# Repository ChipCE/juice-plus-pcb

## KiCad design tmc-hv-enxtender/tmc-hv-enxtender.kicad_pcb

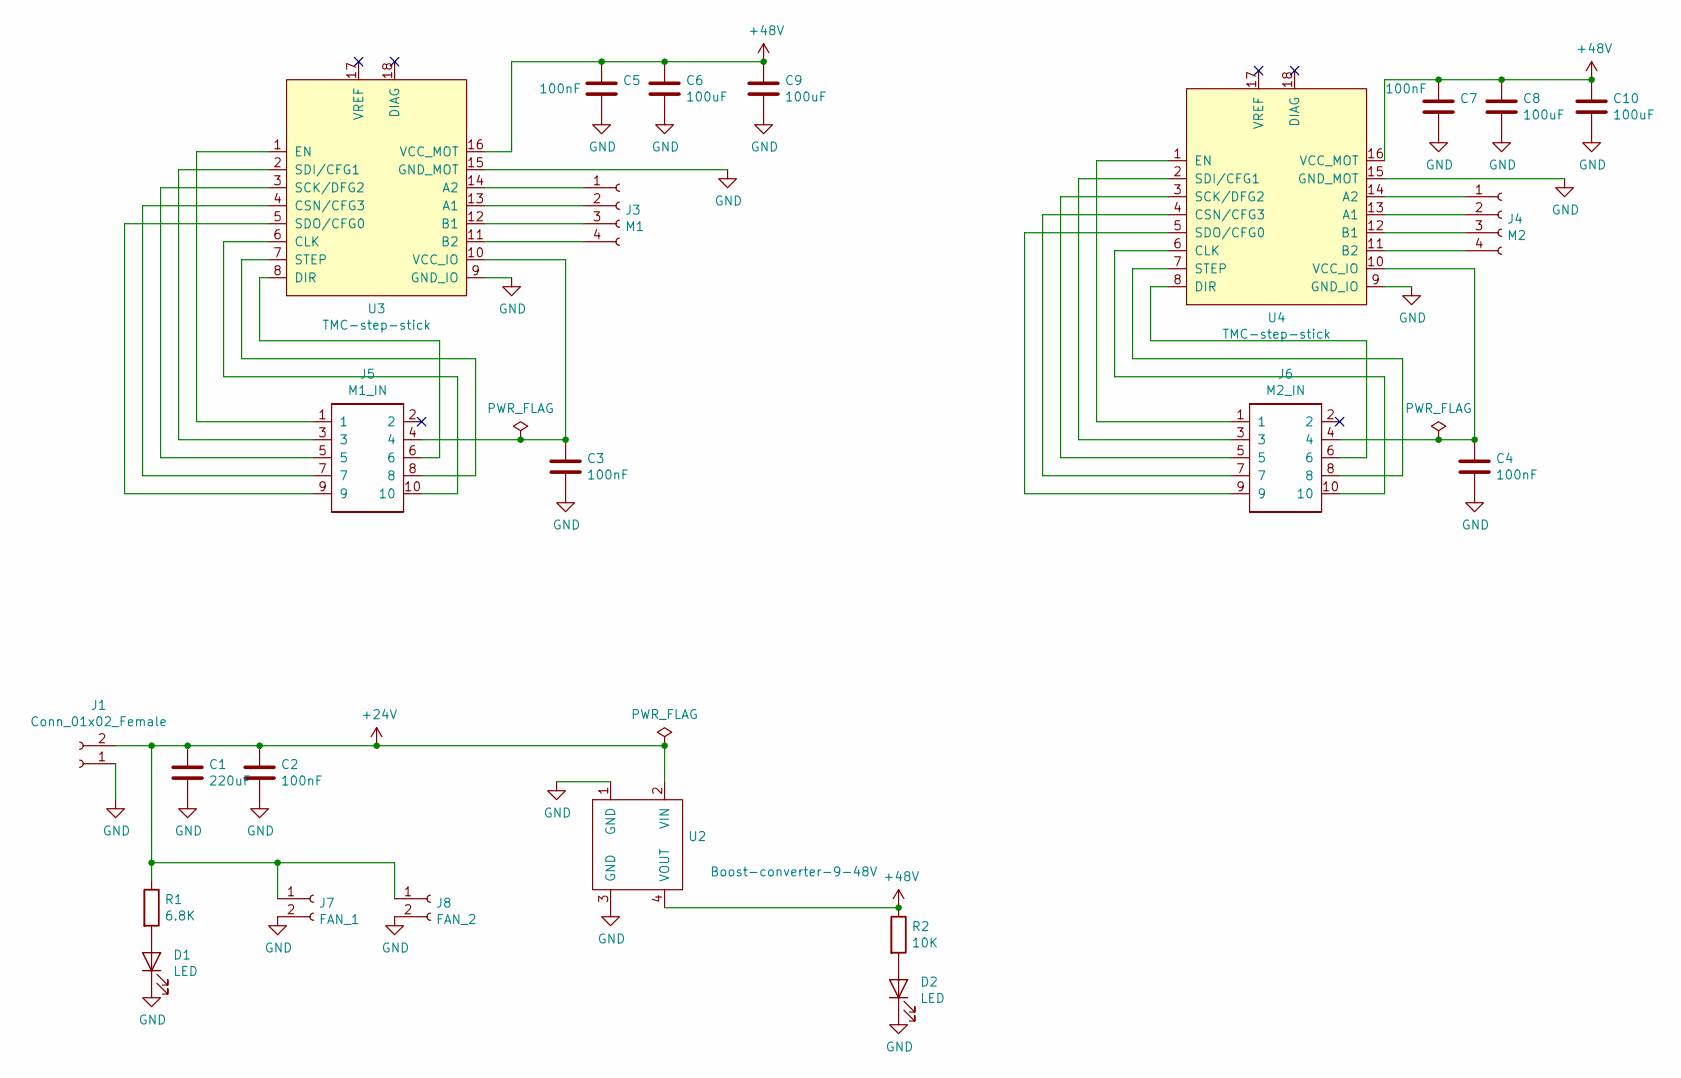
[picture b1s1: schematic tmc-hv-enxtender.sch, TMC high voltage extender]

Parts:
C1: 220uF; CP_Radial_D8.0mm_P3.50mm
C2, C5, C7: 100nF; C_1210_3225Metric
C3, C4: 100nF; C_0805_2012Metric_Pad1.15x1.40mm_HandSolder
C6, C8, C9, C10: 100uF; CP_Radial_D10.0mm_P5.00mm
D1, D2: LED; LED_0805_2012Metric_Castellated
J1: Conn_01x02_Female; TerminalBlock_Phoenix_PT-1,5-2-5.0-H_1x02_P5.00mm_Horizontal
J3: M1; JST_XH_B04B-XH-A_1x04_P2.50mm_Vertical
J4: M2; JST_XH_B04B-XH-A_1x04_P2.50mm_Vertical
J5: M1_IN; IDC-Header_2x05_P2.54mm_Vertical
J6: M2_IN; IDC-Header_2x05_P2.54mm_Vertical
J7: FAN_1; JST_XH_B02B-XH-A_1x02_P2.50mm_Vertical
J8: FAN_2; JST_XH_B02B-XH-A_1x02_P2.50mm_Vertical
R1: 6.8K; R_0805_2012Metric_Pad1.15x1.40mm_HandSolder
R2: 10K; R_0805_2012Metric_Pad1.15x1.40mm_HandSolder
U2: Boost-converter-9-48V; boost-converter-9-48V
U3, U4: TMC-step-stick

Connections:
+24V: C1.1, C2.1, J1.2, J7.1, J8.1, R1.1, U2.2 (VIN)
+48V: C5.1, C6.1, C7.1, C8.1, C9.1, C10.1, R2.1, U2.4 (VOUT), U3.16 (VCC_MOT), U4.16 (VCC_MOT)
GND: C1.2, C2.2, C3.2, C4.2, C5.2, C6.2, C7.2, C8.2, C9.2, C10.2, D1.1 (K), D2.1 (K), J1.1, J7.2, J8.2, U2.1 (GND), U2.3 (GND), U3.9 (GND_IO), U3.15 (GND_MOT), U4.9 (GND_IO), U4.15 (GND_MOT)
unnamed: C3.1, J5.4, U3.10 (VCC_IO)
unnamed: C4.1, J6.4, U4.10 (VCC_IO)
unnamed: D1.2 (A), R1.2
unnamed: D2.2 (A), R2.2
unnamed: J3.1, U3.14 (A2)
unnamed: J3.2, U3.13 (A1)
unnamed: J3.3, U3.12 (B1)
unnamed: J3.4, U3.11 (B2)
unnamed: J4.1, U4.14 (A2)
unnamed: J4.2, U4.13 (A1)
unnamed: J4.3, U4.12 (B1)
unnamed: J4.4, U4.11 (B2)
unnamed: J5.1, U3.1 (EN)
unnamed: J5.3, U3.2 (SDI/CFG1)
unnamed: J5.5, U3.3 (SCK/DFG2)
unnamed: J5.6, U3.8 (DIR)
unnamed: J5.7, U3.4 (CSN/CFG3)
unnamed: J5.8, U3.7 (STEP)
unnamed: J5.9, U3.5 (SDO/CFG0)
unnamed: J5.10, U3.6 (CLK)
unnamed: J6.1, U4.1 (EN)
unnamed: J6.3, U4.2 (SDI/CFG1)
unnamed: J6.5, U4.3 (SCK/DFG2)
unnamed: J6.6, U4.8 (DIR)
unnamed: J6.7, U4.4 (CSN/CFG3)
unnamed: J6.8, U4.7 (STEP)
unnamed: J6.9, U4.5 (SDO/CFG0)
unnamed: J6.10, U4.6 (CLK)

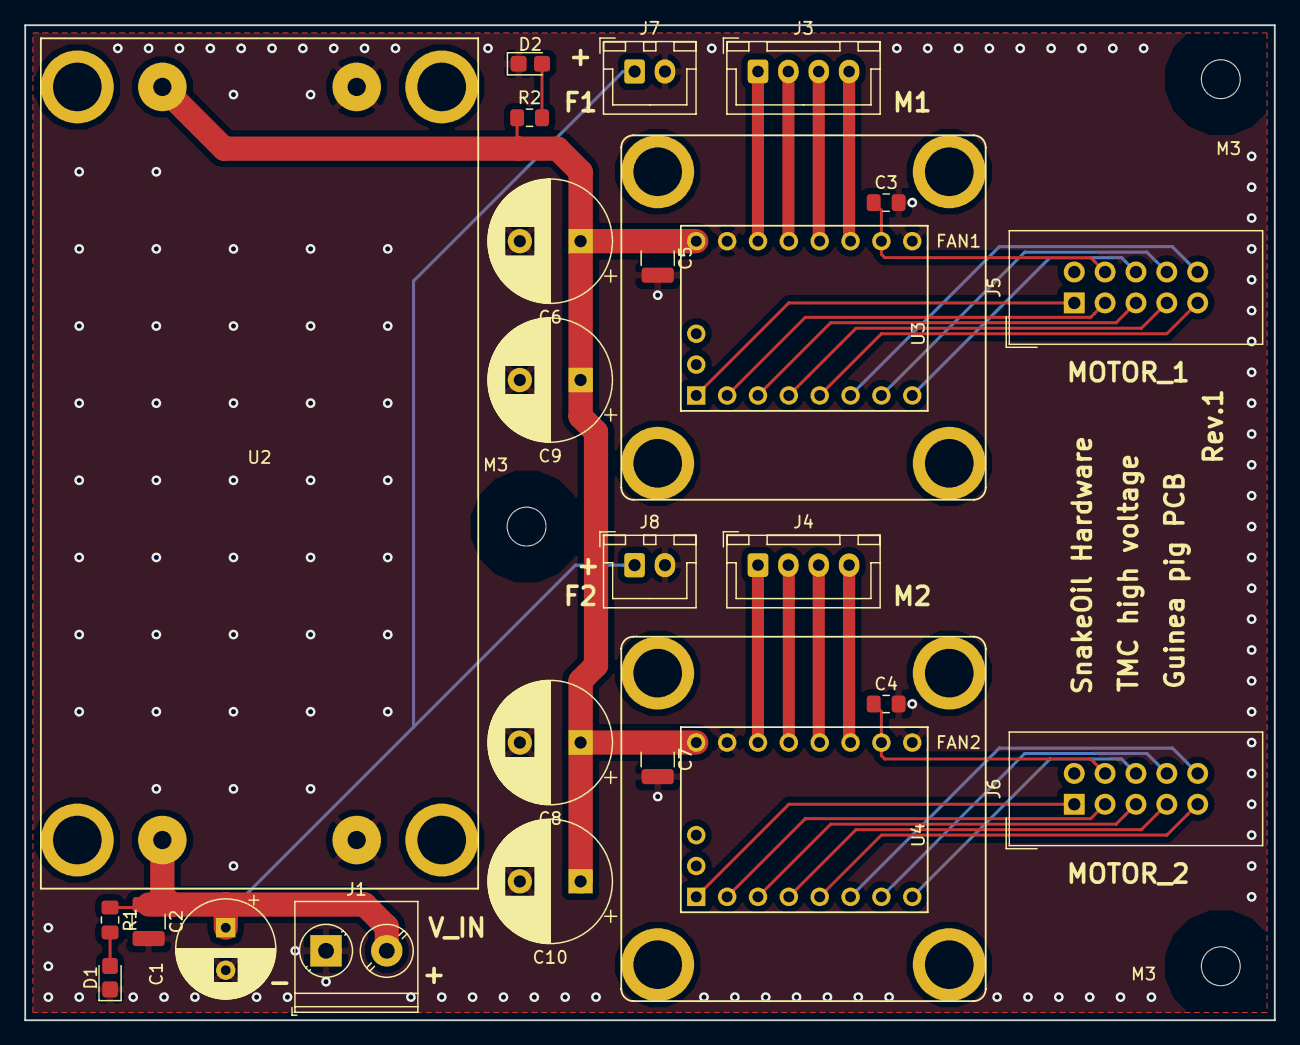
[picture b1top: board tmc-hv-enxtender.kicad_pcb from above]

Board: 2 copper layers, 102.9 x 81.9 mm, 29 parts (0 on the bottom side), 31 nets.

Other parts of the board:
FAN1, FAN2: 3010-fan
M3, M3#2, M3#3: MountingHole_3.2mm_M3

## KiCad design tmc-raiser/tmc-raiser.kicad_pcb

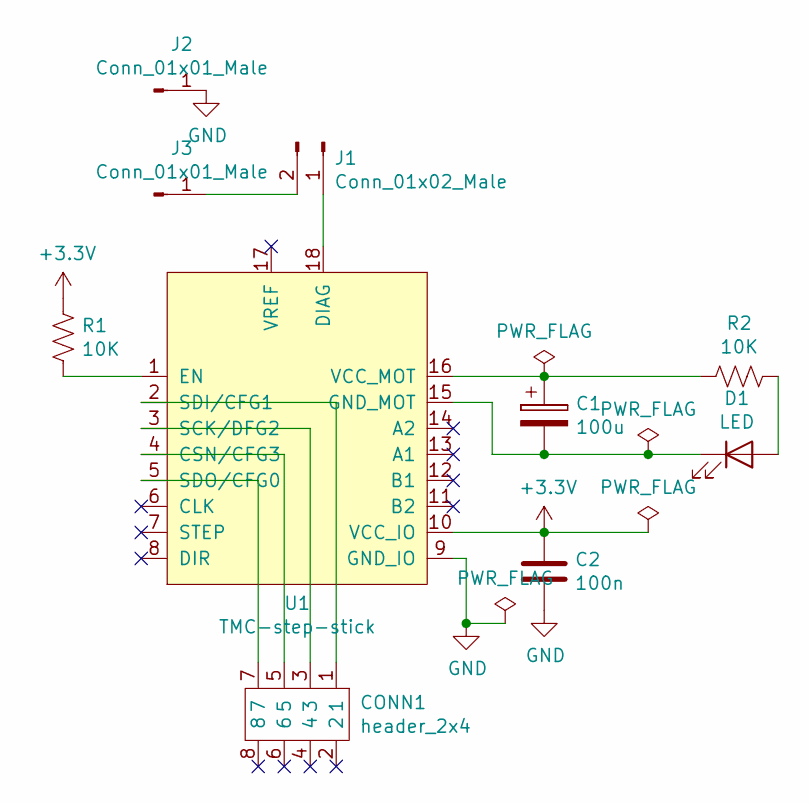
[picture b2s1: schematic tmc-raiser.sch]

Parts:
C1: 100u; C_Elec_10x10.2
C2: 100n; C_0805_2012Metric_Pad1.15x1.40mm_HandSolder
CONN1: header_2x4; PinHeader_2x04_P2.54mm_Vertical
D1: LED; LED_0805_2012Metric_Pad1.15x1.40mm_HandSolder
J1: Conn_01x02_Male; PinHeader_1x02_P2.54mm_Vertical
J2, J3: Conn_01x01_Male; PinHeader_1x01_P2.54mm_Vertical
R1, R2: 10K; R_0805_2012Metric_Pad1.15x1.40mm_HandSolder
U1: TMC-step-stick

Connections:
+3V3: C2.1, R1.1, U1.10 (VCC_IO)
GND: C2.2, J2.1, U1.9 (GND_IO)
unnamed: C1.1, R2.2, U1.16 (VCC_MOT)
unnamed: C1.2, D1.1 (K), U1.15 (GND_MOT)
unnamed: CONN1.1, U1.2 (SDI/CFG1)
unnamed: CONN1.3, U1.3 (SCK/DFG2)
unnamed: CONN1.5, U1.4 (CSN/CFG3)
unnamed: CONN1.7, U1.5 (SDO/CFG0)
unnamed: D1.2 (A), R2.1
unnamed: J1.1, U1.18 (DIAG)
unnamed: J1.2, J3.1
unnamed: R1.2, U1.1 (EN)

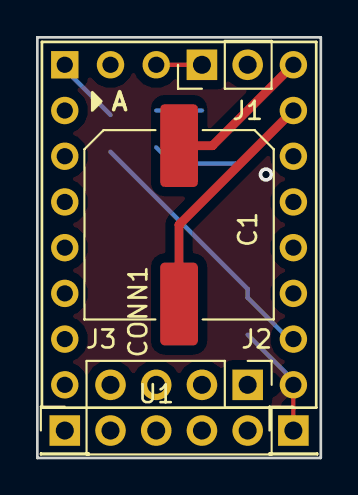
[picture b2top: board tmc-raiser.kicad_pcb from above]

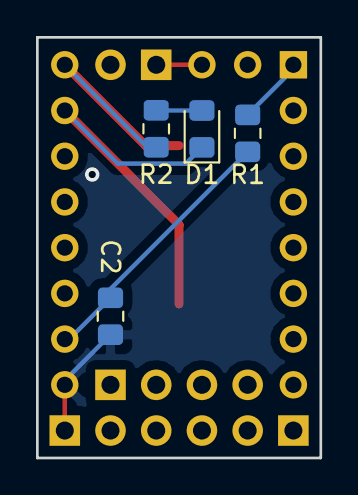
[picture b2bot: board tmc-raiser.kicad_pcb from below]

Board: 4 copper layers, 15.7 x 23.4 mm, 10 parts (4 on the bottom side), 12 nets.

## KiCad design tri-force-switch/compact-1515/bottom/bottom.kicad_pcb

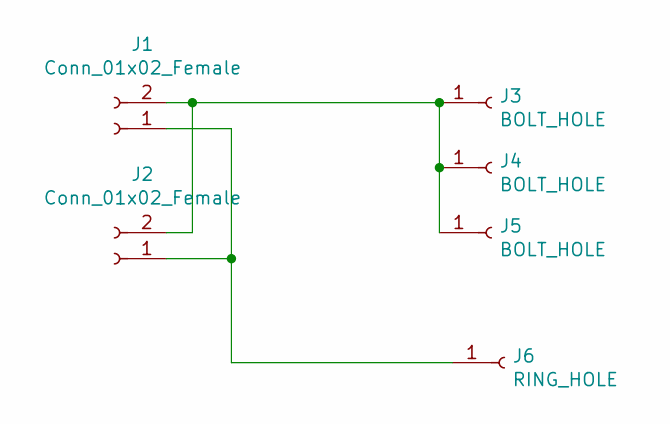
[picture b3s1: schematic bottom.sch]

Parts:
J1, J2: Conn_01x02_Female; solder-pin-th-2pin
J3, J4, J5: BOLT_HOLE; m3-d8-mounting-hole
J6: RING_HOLE; m3-d12-mounter-hole

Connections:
unnamed: J1.1, J2.1, J6.1
unnamed: J1.2, J2.2, J3.1, J4.1, J5.1

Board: 4 copper layers, 6 parts (0 on the bottom side), 2 nets, no tracks yet.
